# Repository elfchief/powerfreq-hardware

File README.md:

## What This Is
This is a mains power frequency monitoring setup. Nominally, mains frequency
is 60Hz (US) or 50Hz (most other places), but the actual frequency varies
over both short periods (where load on the system causes rapid changes), 
and long periods (when power frequency is manually 'corrected' to try to
give an average of exactly 60Hz over sufficiently long periods).

There's no real point to this, other than it being interesting. People having
the same interest were able to make really fascinating visualizations like
this one, though: https://www.youtube.com/watch?v=H7y-oJYpDkM

## Theory of Operation
This circuit has three connections into it:

1. The AC mains @ 120v RMS, on which the measurement is performed, provided 
by standard IEC 60320 'C14' connector.
2. A precision 10MHz reference, against which measurements are made
(presumably from a GPSDO or rubidium reference), provided via a typical SMA
connector, from 50 ohm cable. 
3. A USB connection, over which measurements are communicated, and which also
provides power to the measurement circuit.

The circuit is ultimately a zero-crossing detector, detecting the leading
(positive) edge of the AC sine wave, which feeds into a time-stamp counter
which generates a timestamp for the start of each wave, and outputs that
timestamp as serial data, which is sent to a connected computer for 
analysis and frequency determination.

## Circuit in Detail

### Input and Clamping
Input is at full mains voltage, isolated by a fused 1:1 xVA transformer.
The input is run through a RC low-pass filter and then through a voltage
clamp that caps the voltage at a relatively low level.

We use a voltage clamp here, instead of stepping down the voltage, for two
reasons:
1. We want to trigger as reliably close to the zero crossing as we possibly
can, and the faster the voltage is changing at the time of the zero crossing,
the faster we get past a voltage that is an indeterminite logic state, to one
that is undeniably high. This reduces measurement jitter.
2. Circuit capacitance can make the voltage linger near (but not at) 0v for
a surprisingly long time. The higher drive voltage reduces this effect
significantly, again reducing measurement jitter.

### Trigger and Inverter
The output of the voltage clamp is turned into a logic-level signal, and then
inverted, via a pair of discrete transistors, eventually resulting in a 60PPS
output at 3.3v (though this should work identically at 5v). There is some
delay caused by these operations, but that delay is fairly stable once
characterized, and can be subtracted out at the processing stage. 

The 3.3v for the logic is supplied by the USB connection via the FTDI chip
(see below).

The clamp and trigger circuitry is courtesy of Charles Steinmetz and is documented
[here](http://www.ko4bb.com/manuals/98.248.63.64/Simple_AC_mains_zero_cross_detector.pdf)

### picPET
The picPET is a simple timestamp counter (TSC) in 8 pin form. It is a PIC
microcontroller based chip that uses a precision 10MHz signal as its system
clock, and outputs timestamps for the rising edge of signals on its input
pin. The timestamps geerated are accurate to within ~400ns, and are output
as low voltage RS232 signals (otput voltage == Vcc).

See [here](http://www.leapsecond.com/pic/picpet.htm) for more details on the picPET

The picPET is also driven from the FTDI chip.

### FTDI
We are using a carrier board to mount a FTDI USB-to-serial chip. The carrier
board contains all needed decoupling caps, isolation, and connectors needed
for the upstream USB connection. The connector names on the schematic match
those of the actual chip.

The FTDI chip has an internal 3.3v regulator that outputs 3.3v for use by
other circuitry, and can provide up to 50mA of current. The board itself
can be jumpered to use (and supply to the circuit) either 3.3v or 5v. The
lower voltage has been chosen to allow the picPET chip to have a lower
trigger voltage on its input clock, since the outputs from disciplined 
sources are generally weak if not externally amplified.

Rough calculations say that 50mA should be enough to drive the circuit, but
if this turns out to be a problem, it can be jumpered to use 5v with no
further changes, beyond possibly having to boost the input clock.

The FTDI chip appears to the attached computer as a standard serial port,
and sends the output serial data from the picPET directly to it with minimal
processing.

The carrier board being used is a MikroElektronika 483. The datasheet for that
board is [here](http://www.mouser.com/ds/2/272/usb_uart_manual_v100-32094.pdf). The
specific FTDI chip provided by that carrier board is the FT232RL, and the 
datasheet for that is [here](http://www.ftdichip.com/Support/Documents/DataSheets/ICs/DS_FT232R.pdf).
We are using the FT232RL in its default configuration.

## Open Questions
A slightly diminished version of this design is currently running on a
breadboard without issue, so it's fairly certain the design works, at
least in a general sense.

Things I don't know:

* Is the fuse on the line side of the transformer sufficient for the 
transformer's inrush current?

* Assuming there's sufficient clearance in the PCB laytout around the line
side of the transformer, is this design 'safe'? Is there additional 
isolation we could do (without adding jitter or phase noise)?

* Does the isolated side of the transformer also need a fuse?

* What voltage rating should C1 and C5 be? Do they have to take the full
line voltage?

* Where is the line in the sand where 'low voltage' starts? Is C2 the
dividing line for that?

* What the heck is D2 for? It was on the reference circuit I borrowed, but
I don't actually know the reason for it.

* Are there other stupidities here, or large improvements that could be made?

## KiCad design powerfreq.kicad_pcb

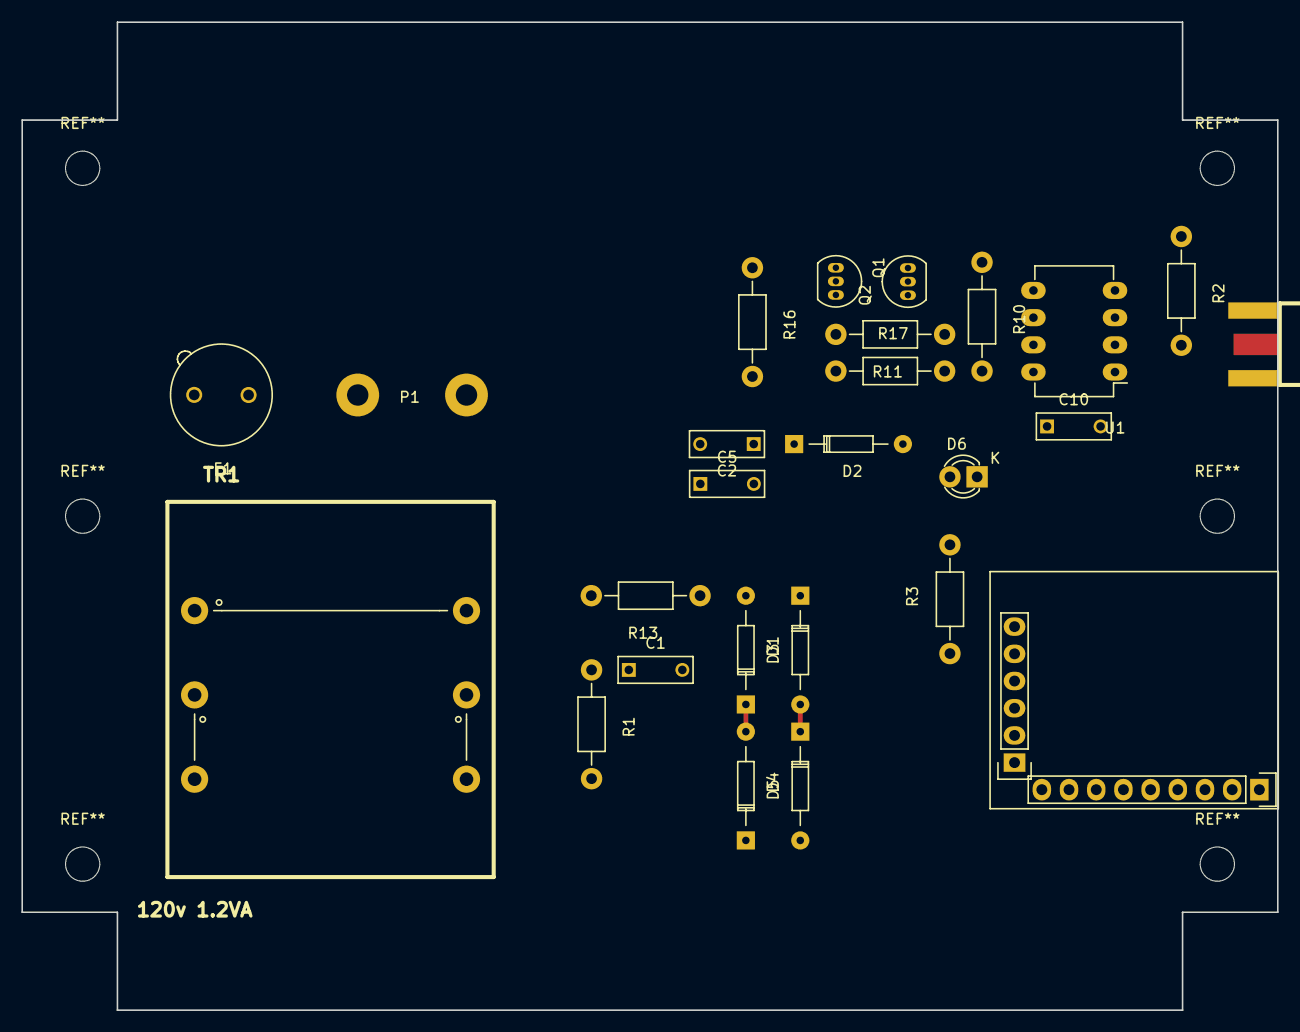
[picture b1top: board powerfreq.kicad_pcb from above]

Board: 2 copper layers, 117.3 x 92.3 mm, 26 parts (0 on the bottom side), 20 nets.

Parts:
C1, C10: 100nF; C_Rect_L7_W2.5_P5
C2, C5: 10nF; C_Rect_L7_W2.5_P5
D1, D2, D3, D4, D5: 1N4148; Diode_DO-35_SOD27_Horizontal_RM10
D6: LED; LED-3MM
F1: 50mA; Fuseholder_Fuse_TR5_Littlefuse-No560_No460
J1: SMA; SMA_EDGE
P1: CONN_01X03; WireConnection_2.00mmDrill
Q1, Q2: 2N3904; TO-92_Inline_Narrow_Oval
R1: 2k 1W; Resistor_Horizontal_RM10mm
R2: 51; Resistor_Horizontal_RM10mm
R3, R10, R16: 1k; Resistor_Horizontal_RM10mm
R11: 2.2k; Resistor_Horizontal_RM10mm
R13: 20k 2W; Resistor_Horizontal_RM10mm
R17: 250; Resistor_Horizontal_RM10mm
TR1: 120v 1.2VA; 161E120
U1: picPET-03; DIP-8_W7.62mm_LongPads
U2: MIKROE-483; mikroe-483

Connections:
10MHz: J1.1, R2.2, U1.2
60PPS: Q2.3, R10.1, U1.5
+3V3: C10.2, R3.1, R10.2, R17.2, U1.1, U1.3, U1.4, U2.2-5
CLAMP: C2.2, C5.1, D1.2, D3.1, R13.1
GND: C1.2, C5.2, C10.1, D2.2, D4.1, D5.2, J1.0, J1.2, Q1.2, Q2.2, R2.1, TR1.3, U1.8, U2.2-6
unnamed: C1.1, R1.1, R13.2
unnamed: C2.1, D2.1, R16.2
unnamed: D1.1, D4.2
unnamed: D3.2, D5.1
unnamed: D6.1, U2.3-1, U2.3-2
unnamed: D6.2, R3.2
unnamed: F1.1, P1.1
unnamed: F1.2, TR1.1
unnamed: P1.2, TR1.2
unnamed: Q1.1, R16.1
unnamed: Q2.1, R11.1
unnamed: R1.2, TR1.6
unnamed: TR1.4, TR1.5
SERIAL_RX: U1.6, U2.2-2
TRIG: Q1.3, R11.2, R17.1

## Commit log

2016-04-16 initial schematic and board layout
2016-04-17 add picPET chip and SMA connector
2016-04-18 Beginnings of proper layout, new footprints for transformer and picPET.
2016-04-25 Set up layout for Hammond RL6335 box, add FTDI daughter board, and footprint fixups.
2016-04-25 Ignore backup files.
2016-04-26 New layout, power on top, I/O on right side
2016-04-26 Add track routing, and a few other fixups.
2016-04-29 add README with explanation and open question
2016-04-29 Added pdf of schematic
2016-05-01 Add links to all the datasheets of ICs
2016-05-04 Added Charles Steinmetz's LTspice model
